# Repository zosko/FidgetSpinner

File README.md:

# FidgetSpinner
PCB Fidget Spinner

## Scheme

## Board

## PCB Preview
Top layer|Bottom layer
---------|---------
|

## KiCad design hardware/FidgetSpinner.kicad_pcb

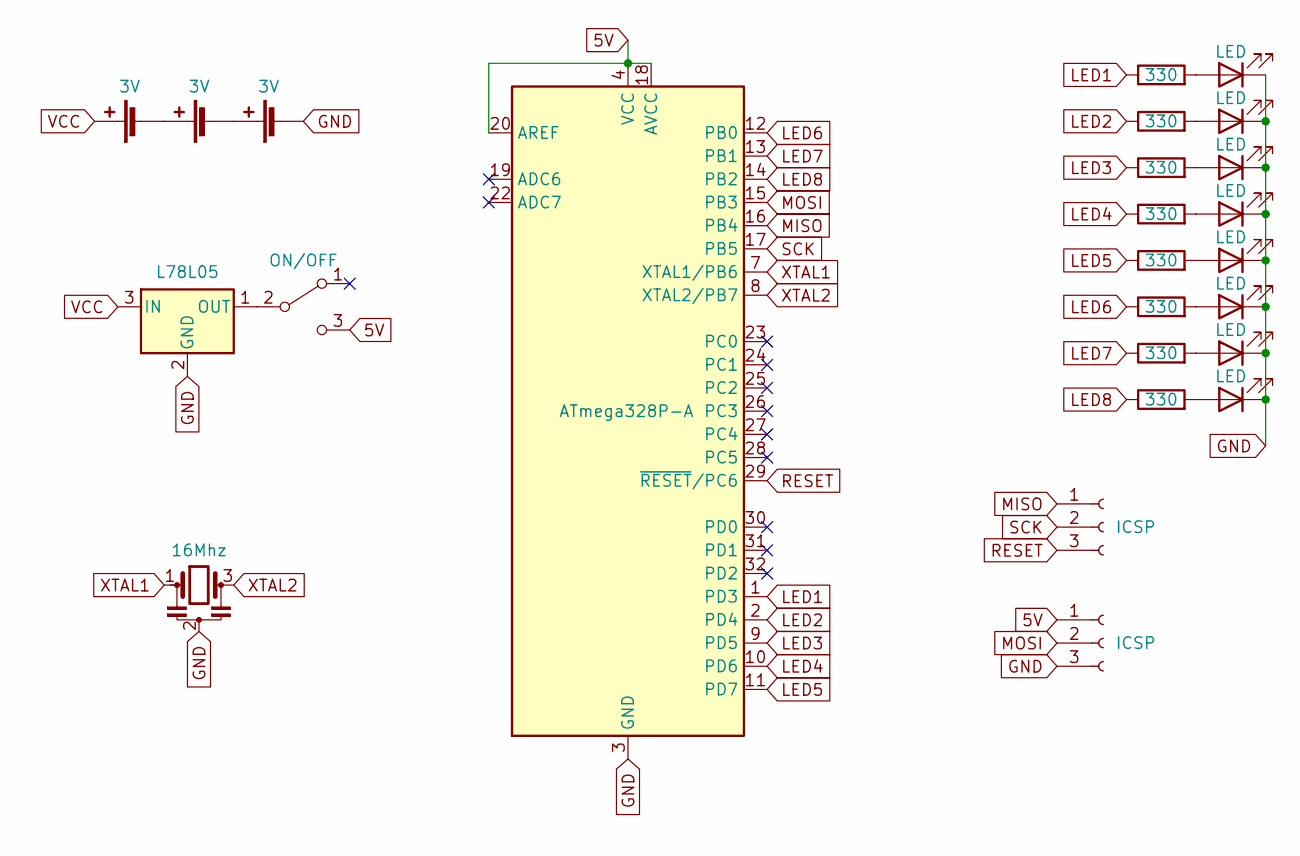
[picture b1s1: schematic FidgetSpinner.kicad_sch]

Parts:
BT1, BT2, BT3: 3V; BatteryHolder_Keystone_3034_1x20mm
D1, D2, D3, D4, D5, D6, D7, D8: LED; LED_0805_2012Metric_Pad1.15x1.40mm_HandSolder
J1, J2: ICSP; PinHeader_1x03_P2.54mm_Vertical
R1, R2, R3, R4, R5, R6, R7, R8: 330; R_0805_2012Metric_Pad1.20x1.40mm_HandSolder
SW1: ON/OFF; SW_SPDT_PCM12
U1: ATmega328P-A; TQFP-32_7x7mm_P0.8mm
U2: L78L05; SOT-89-3
Y1: 16Mhz; Resonator_SMD_Murata_CSTxExxV-3Pin_3.0x1.1mm_HandSoldering

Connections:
5V: J2.1, SW1.3 (C), U1.4 (VCC), U1.6 (VCC), U1.18 (AVCC), U1.20 (AREF)
GND: BT3.2 (-), D1.1 (K), D2.1 (K), D3.1 (K), D4.1 (K), D5.1 (K), D6.1 (K), D7.1 (K), D8.1 (K), J2.3, U1.3 (GND), U1.5 (GND), U1.21 (GND), U2.2 (GND), Y1.2
LED1: R1.1, U1.1 (PD3)
LED2: R2.1, U1.2 (PD4)
LED3: R3.1, U1.9 (PD5)
LED4: R4.1, U1.10 (PD6)
LED5: R5.1, U1.11 (PD7)
LED6: R6.1, U1.12 (PB0)
LED7: R7.1, U1.13 (PB1)
LED8: R8.1, U1.14 (PB2)
MISO: J1.1, U1.16 (PB4)
MOSI: J2.2, U1.15 (PB3)
unnamed: BT1.2 (-), BT2.1 (+)
unnamed: BT2.2 (-), BT3.1 (+)
unnamed: D1.2 (A), R1.2
unnamed: D2.2 (A), R2.2
unnamed: D3.2 (A), R3.2
unnamed: D4.2 (A), R4.2
unnamed: D5.2 (A), R5.2
unnamed: D6.2 (A), R6.2
unnamed: D7.2 (A), R7.2
unnamed: D8.2 (A), R8.2
unnamed: SW1.2 (B), U2.1 (OUT)
RESET: J1.3, U1.29 (~RESET/PC6)
SCK: J1.2, U1.17 (PB5)
VCC: BT1.1 (+), U2.3 (IN)
XTAL1: U1.7 (XTAL1/PB6), Y1.1
XTAL2: U1.8 (XTAL2/PB7), Y1.3

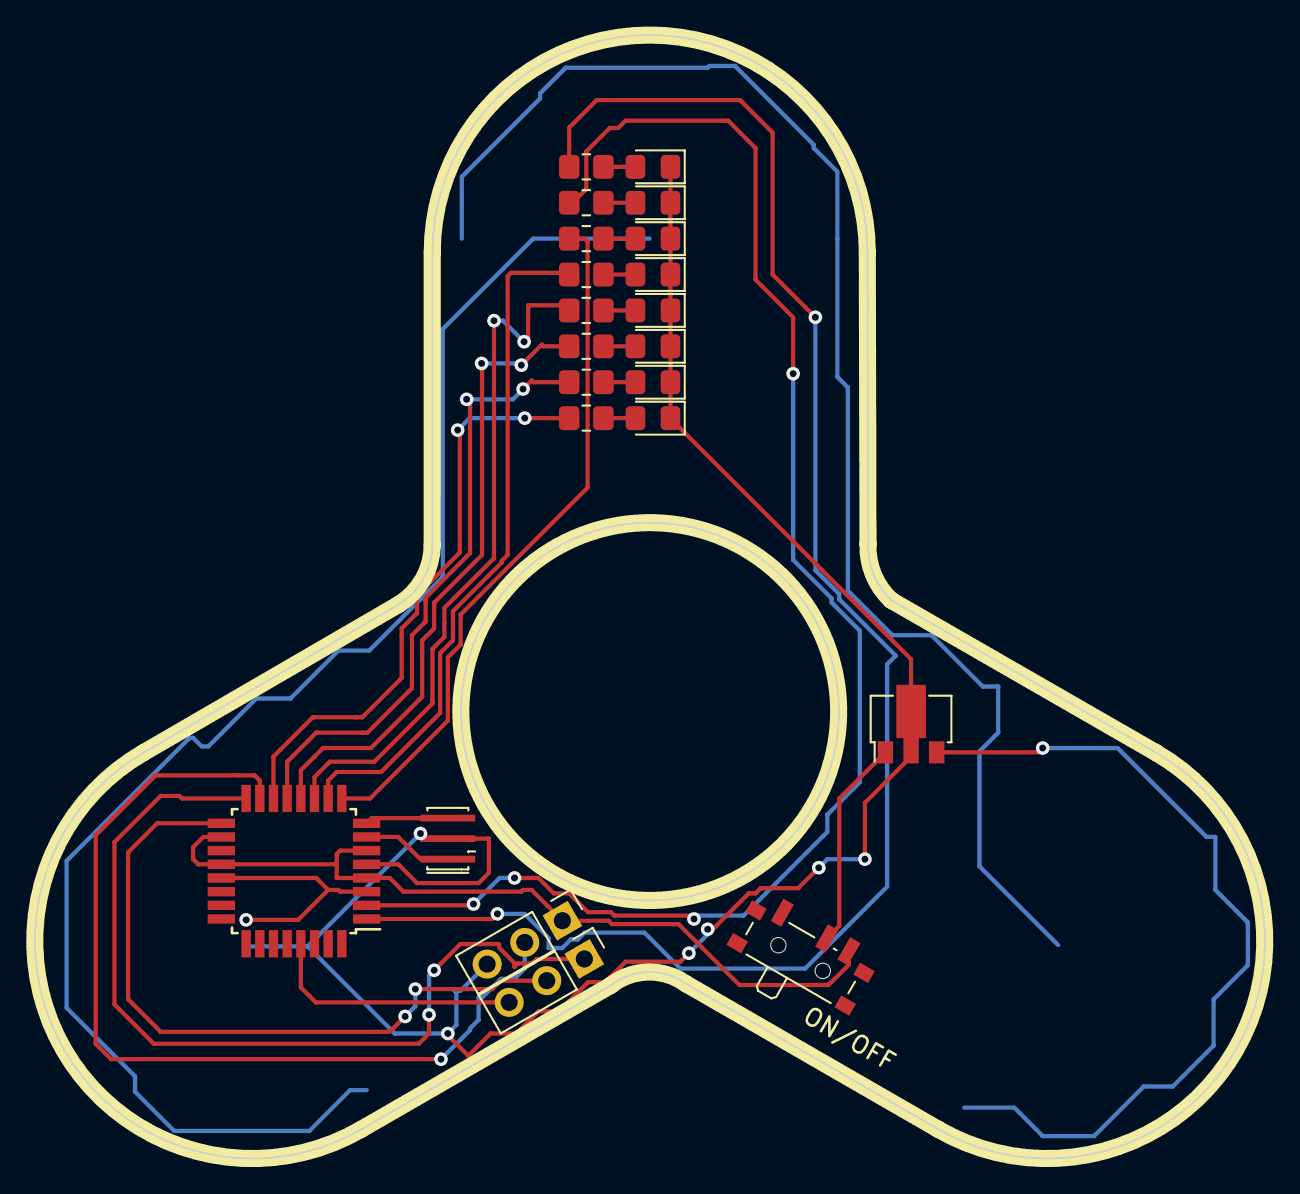
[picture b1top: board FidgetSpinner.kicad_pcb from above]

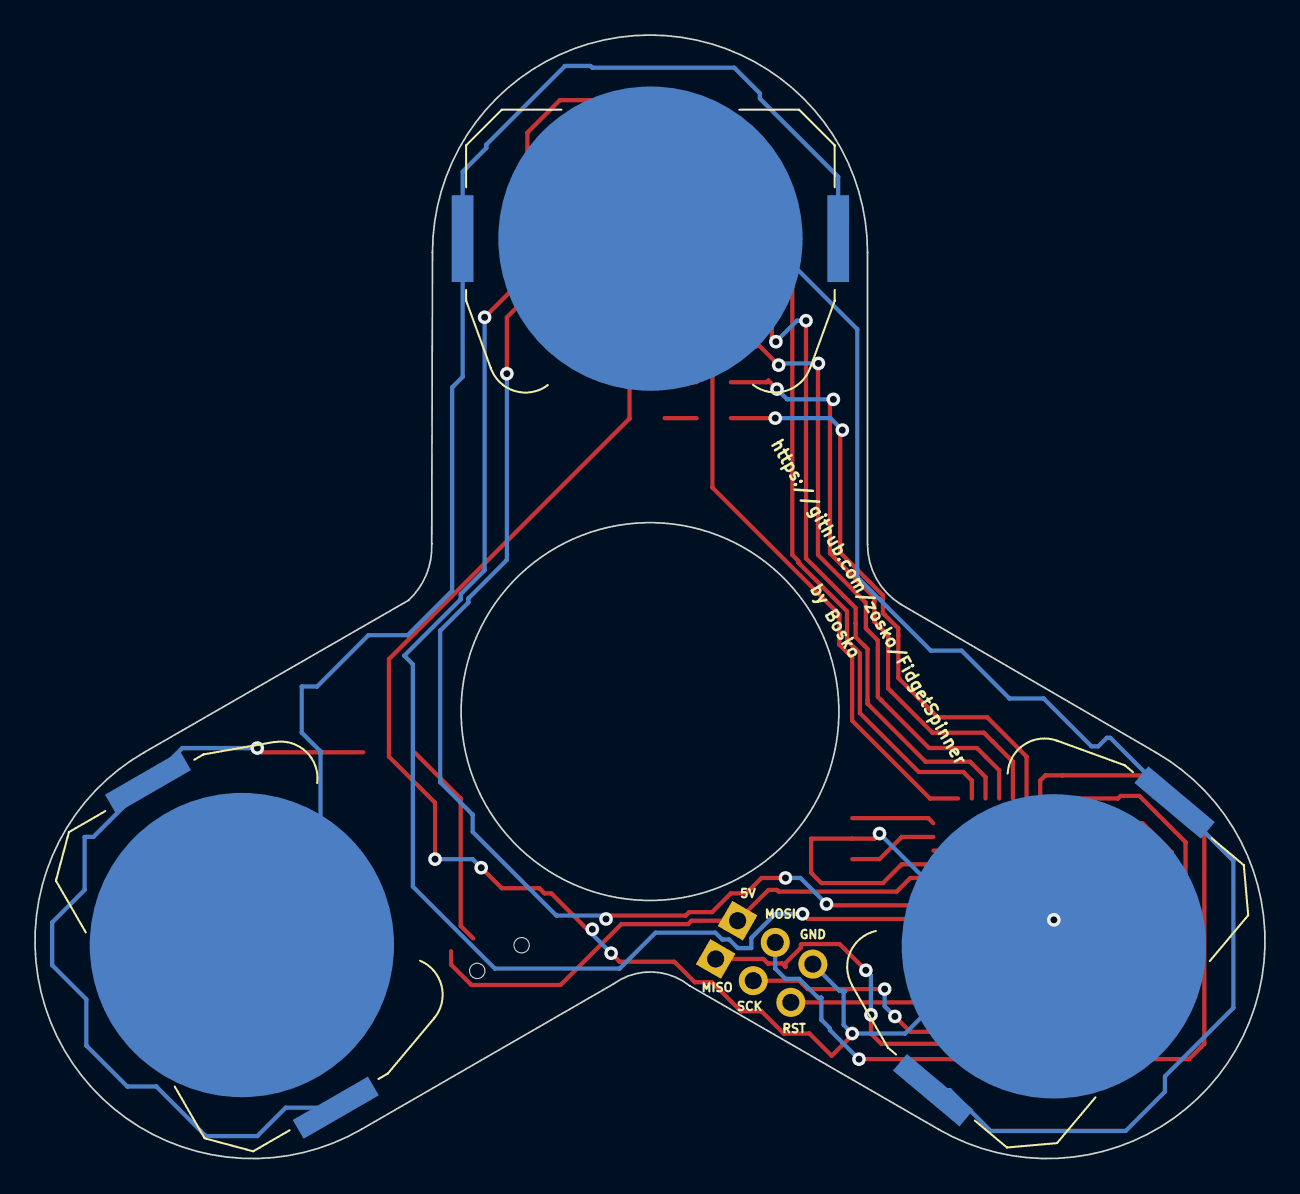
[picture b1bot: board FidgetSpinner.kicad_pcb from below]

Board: 2 copper layers, 71.9 x 65.7 mm, 25 parts (3 on the bottom side), 28 nets.

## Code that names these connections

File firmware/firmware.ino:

const int LED1 = 3;
const int LED2 = 4;
const int LED3 = 5;
const int LED4 = 6;
const int LED5 = 7;
const int LED6 = 8;
const int LED7 = 9;
const int LED8 = 10;

void setup() {
  pinMode(LED1, OUTPUT);
  pinMode(LED2, OUTPUT);
  pinMode(LED3, OUTPUT);
  pinMode(LED4, OUTPUT);
  pinMode(LED5, OUTPUT);
  pinMode(LED6, OUTPUT);
  pinMode(LED7, OUTPUT);
  pinMode(LED8, OUTPUT);
}

void loop() {
  S();
  Sp();
  L();
  Sp();
  I();
  Sp();
  C();
  Sp();
  E();
  Sp();
  Sp();
  Sp();
  Sp();
  Sp();
  Sp();
  Sp();
  Sp();
  Sp();
  Sp();
  Sp();
  Sp();
  Sp();
}

void SLICE() {
  Sp();
  signal(1, 0, 0, 0, 0, 0, 0, 0);
  signal(1, 1, 0, 0, 0, 0, 0, 0);
  signal(1, 1, 1, 0, 0, 0, 0, 0);
  signal(1, 1, 1, 1, 0, 0, 0, 0);
  signal(1, 1, 1, 1, 1, 0, 0, 0);
  signal(1, 1, 1, 1, 1, 1, 0, 0);
  signal(1, 1, 1, 1, 1, 1, 1, 0);
  signal(1, 1, 1, 1, 1, 1, 1, 1);
  signal(1, 1, 1, 1, 1, 1, 1, 1);
  signal(1, 1, 1, 1, 1, 1, 1, 0);
  signal(1, 1, 1, 1, 1, 1, 0, 0);
  signal(1, 1, 1, 1, 1, 0, 0, 0);
  signal(1, 1, 1, 1, 0, 0, 0, 0);
  signal(1, 1, 1, 0, 0, 0, 0, 0);
  signal(1, 1, 0, 0, 0, 0, 0, 0);
  signal(1, 0, 0, 0, 0, 0, 0, 0);
  Sp();
}

void C() {
  signal(0, 1, 1, 1, 1, 1, 1, 0);
  signal(1, 0, 0, 0, 0, 0, 0, 1);
  signal(1, 0, 0, 0, 0, 0, 0, 1);
  signal(1, 0, 0, 0, 0, 0, 0, 1);
  signal(0, 1, 0, 0, 0, 0, 1, 0);
}

void E() {
  signal(1, 1, 1, 1, 1, 1, 1, 1);
  signal(1, 0, 0, 0, 1, 0, 0, 1);
  signal(1, 0, 0, 0, 1, 0, 0, 1);
  signal(1, 0, 0, 0, 1, 0, 0, 1);
  signal(1, 0, 0, 0, 0, 0, 0, 1);
}

void I() {
  signal(1, 0, 0, 0, 0, 0, 0, 1);
  signal(1, 1, 1, 1, 1, 1, 1, 1);
  signal(1, 0, 0, 0, 0, 0, 0, 1);
}

void L() {
  signal(1, 1, 1, 1, 1, 1, 1, 1);
  signal(0, 0, 0, 0, 0, 0, 0, 1);
  signal(0, 0, 0, 0, 0, 0, 0, 1);
  signal(0, 0, 0, 0, 0, 0, 0, 1);
  signal(0, 0, 0, 0, 0, 0, 0, 1);
}

void S() {
  signal(0, 1, 1, 0, 0, 0, 0, 1);
  signal(1, 0, 0, 1, 0, 0, 0, 1);
  signal(1, 0, 0, 1, 0, 0, 0, 1);
  signal(1, 0, 0, 1, 0, 0, 0, 1);
  signal(1, 0, 0, 0, 1, 1, 1, 0);
}

void Sp() {
  signal(0, 0, 0, 0, 0, 0, 0, 0);
  signal(0, 0, 0, 0, 0, 0, 0, 0);
  signal(0, 0, 0, 0, 0, 0, 0, 0);
  signal(0, 0, 0, 0, 0, 0, 0, 0);
  signal(0, 0, 0, 0, 0, 0, 0, 0);
}

void signal(int P1, int P2, int P3, int P4, int P5, int P6, int P7, int P8) {

  digitalWrite(LED1, P1);
  digitalWrite(LED2, P2);
  digitalWrite(LED3, P3);
  digitalWrite(LED4, P4);
  digitalWrite(LED5, P5);
  digitalWrite(LED6, P6);
  digitalWrite(LED7, P7);
  digitalWrite(LED8, P8);

  delay(1);
}

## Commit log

2022-10-04 update code
